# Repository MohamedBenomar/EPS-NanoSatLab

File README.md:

# Electrical Power System (EPS) for the NanoSatLab of the Universitat Politècnica de Catalunya (UPC)

Study and validate a design of a Electrical Power System for Nanosatellites using Supercapacitors technology as a source for systems that require high currents for a short time, together with Lithium-Ion batteries.

## Table of Contents

- [CADS](#cads)
- [Docs](#docs)
- [Firmware](#firmware)
- [Hardware](#hardware)
- [Validation](#validation)

## CADS

This folder section the 3D model of the designed PCB and the 3D model of an encapsulate for the system.

## Docs

This section includes the datasheets of the components used in the design, a real picture of the system indicating the differents blocks and the paper about the project.

## Firmware

This section includes the firmware for the ESP using an STM32 microcontroller.

## Hardware

This section includes the hardware files of the system using the open-source software KiCad.

## Validation

This section contains the validation report of the system.

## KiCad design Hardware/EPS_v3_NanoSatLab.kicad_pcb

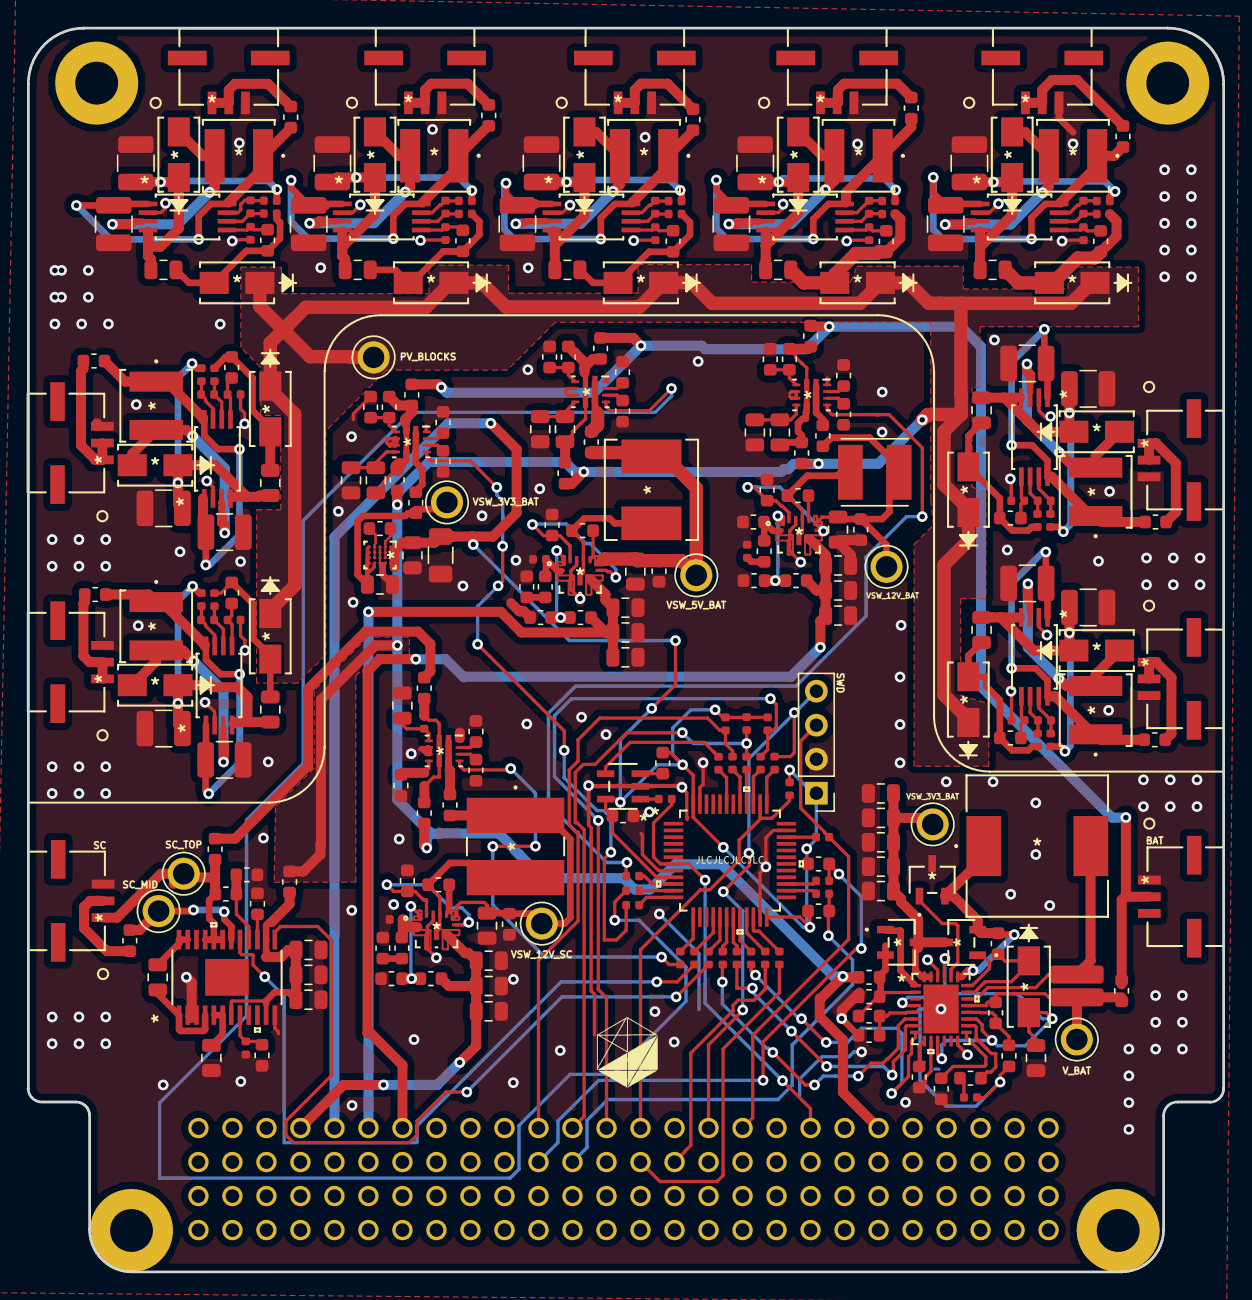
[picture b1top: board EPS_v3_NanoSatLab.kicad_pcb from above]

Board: 2 copper layers, 89.3 x 92.9 mm, 295 parts (0 on the bottom side), 198 nets.

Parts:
C201, C301, C302, C305, C306, C307, C308, C309, C313, C314, C317: 100 nF; C_0603_1608Metric
C303, C304, C312, C322, C324, C325, C327, C333, C401, C403, C404, C405, C502, C503, C505, C506, C508, C509: 10 uF; C_0805_2012Metric
C310, C311, C318: 2.2 uF; C_0603_1608Metric
C315, C316: 47 nF; C_0603_1608Metric
C319, C320: 62 pF; C_0402_1005Metric
C321, C323, C326, C330, C331, C332: 22 uF; C_0805_2012Metric
C328: 39 nF; C_0402_1005Metric
C329: 82 pF; C_0603_1608Metric
C334: 47 uF; C_1206_3216Metric
C402: 470 pF; C_0402_1005Metric
C501: 0.1 uF; C_0603_1608Metric
C504: 0.01 uF; C_0402_1005Metric
C507: 0.22 uF; C_0603_1608Metric
C601, C602, C603, C610, C611, C612, C619, C620, C621: 100 uF; C_1210_3225Metric
C604, C605, C606, C613, C614, C615, C622, C623, C624: 1 uF; C_0402_1005Metric
C607, C608, C609, C616, C617, C618, C625, C626, C627: 150 uF; C_1210_3225Metric
D501: 1A; DO-214BA-2
D601, D602, D603, D604, D605, D606, D607, D608, D609, D610, D611, D612, D613, D614, D615, D616, D617, D618: Vf=0.3V and If=3A; DO-214AB-2
J101, J102, J103, J104, J105, J106, J107, J108, J109, J111, J112: 502382-0370; MOLEX_502382-0370
J110: PC104
J201: SWD; PinHeader_1x04_P2.54mm_Vertical
L301: 3.2 uH; IND_FP3-3R3-R
L302: 6 uH; PM628S-100
L303: 2.7 uH; IND_LQH5BPN2R7NT0L
L304: 1 uH; L_0603_1608Metric
L401: 3.3 uH; L_0805_2012Metric
L501: 2.1 uH; NR10050T2R1N
L601, L602, L603, L604, L605, L606, L607, L608, L609: 47 uH; NRS5020T4R7MMGJ
Q501: INFET; DMN1019USN-7(TSOT-26-6)
Q502: T_NMOS; DMN1019USN-7(TSOT-26-6)
Q503: B_NMOS; DMN1019USN-7(TSOT-26-6)
R201, R202, R203, R204: 100 kΩ; R_0402_1005Metric
R205, R211, R227, R311, R312, R319, R320, R328, R329: 10 kΩ; R_0603_1608Metric
R206, R207, R208, R209, R210, R212, R213, R214, R215, R216, R217, R218, R219, R220, R221, R224, R225, R226: 0 Ω; R_0402_1005Metric
R222, R223: 33 Ω; R_0402_1005Metric
R301, R302, R303, R304, R315, R316, R321, R322, R323, R324, R330, R338, R401, R404, R407, R501, R510, R601, R602, R603, R619, R620, R621, R637, R638, R639: 0 Ω; R_0603_1608Metric
R305, R307: 12 kΩ; R_0402_1005Metric
R306: 40.2 kΩ; R_0603_1608Metric
R308: 7.5 kΩ; R_0805_2012Metric
R309, R317, R326: 5.1 kΩ; R_0805_2012Metric
R310, R318, R327: 15 kΩ; R_0805_2012Metric
R313, R314, R325, R331: 18 kΩ; R_0603_1608Metric
R332: 19.6 kΩ; R_0603_1608Metric
R333: 20.5 kΩ; R_0603_1608Metric
R334: 357 kΩ; R_0603_1608Metric
R335, R337, R341: 48.7 kΩ; R_0603_1608Metric
R336, R340: 931 kΩ; R_0603_1608Metric
R339: 34 kΩ; R_0603_1608Metric
R402: 3.57 kΩ; R_0603_1608Metric
R403: 142 kΩ; R_0603_1608Metric
R405: 2.21 MΩ; R_0603_1608Metric
R406: 301 kΩ; R_0603_1608Metric
R502: 1.5 MΩ; R_0603_1608Metric
R503, R507, R508: 1 MΩ; R_0603_1608Metric
R504: 86.6 kΩ; R_0603_1608Metric
R505: 75 kΩ; R_0603_1608Metric
R506: 3.36 kΩ; R_0603_1608Metric
R509: 22 mΩ; R_0815_2038Metric
R604, R605, R606, R607, R608, R609, R622, R623, R624, R625, R626, R627, R640, R641, R642, R643, R644, R645: 1 kΩ; R_0402_1005Metric
R610, R611, R612, R628, R629, R630, R646, R647, R648: 33.2 mΩ; R_0805_2012Metric
R613, R615, R617, R631, R633, R635, R649, R651, R653: 2 MΩ; R_0603_1608Metric
R614, R616, R618, R632, R634, R636, R650, R652, R654: 680 kΩ; R_0402_1005Metric
TP301, TP302, TP303, TP304, TP401, TP402, TP501, TP502, TP601: TestPoint; TESTPOINT_5013
U201: STM32L412C8T6
U202: MCP1320T-29LE_OT; MCP1320T-29LE&slash_OT
U301, U302, U303, U306: TPS2121RUXR
U304, U305, U307: TPS61288RQQR
U308: YFF0020AJAF; TPS630242YFFR
U401: LTC3128; LTC3128EFE-PBF
U501: LTC4013EUFD-PBF
U601, U602, U603, U604, U605, U606, U607, U608, U609: SPV1040T

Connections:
/5V_BAT: C321.1, C323.1, C326.1, J110.P$41, R334.1, U304.5
/12V_BAT: C330.1, C331.1, C332.1, J110.P$39, R340.1, U307.5
/12V_SC: C322.1, C324.1, C327.1, J110.P$45, R336.1, U305.5
/EPS - Batteries/BAT_CHG_ISMON: R217.2, U501.6
/EPS - Batteries/BAT_CHG_STAT0: R218.2, U501.7
/EPS - Batteries/BAT_CHG_STAT1: R210.2, U501.8
/EPS - Batteries/INTVCC: C509.2, D501.2, U501.4, U501.11, U501.17, U501.25
/EPS - Batteries/V_BAT: J111.2, R304.2, R316.2, R324.2, R510.1
/EPS - Converters/SW_3V3_BAT_uC: R213.2, U306.9
/EPS - Converters/SW_5V_BAT_uC: R207.2, U302.9
/EPS - Converters/SW_12V_BAT_uC: R212.2, U303.9
/EPS - Converters/SW_12V_SC_uC: R208.2, U301.9
/EPS - Converters/VSW_3V3_BAT: C325.1, R338.1, R338.2, TP304.1, U306.1, U306.8, U308.D4, U308.E1, U308.E2, U308.E3, U308.E4
/EPS - Converters/VSW_5V_BAT: R322.2, U302.1, U302.8
/EPS - Converters/VSW_12V_BAT: R330.2, U303.1, U303.8
/EPS - Converters/VSW_12V_SC: R321.2, U301.1, U301.8
/EPS - MCU/*PFO_SC: R209.2, U401.13
/EPS - MCU/PGOOD_SC: R214.2, U401.17
/EPS - MCU/WDI: R221.2, U202.4
/EPS – MPPT/PV_Array_X_1: J101.1, J101.2, R601.2
/EPS – MPPT/PV_Array_X_2: J104.1, J104.2, R619.2
/EPS – MPPT/PV_Array_X_3: J107.1, J107.2, R637.2
/EPS – MPPT/PV_Array_Y_1: J102.1, J102.2, R602.2
/EPS – MPPT/PV_Array_Y_2: J105.1, J105.2, R620.2
/EPS – MPPT/PV_Array_Y_3: J108.1, J108.2, R638.2
/EPS – MPPT/PV_Array_Z_1: J103.1, J103.2, R603.2
/EPS – MPPT/PV_Array_Z_2: J106.1, J106.2, R621.2
/EPS – MPPT/PV_Array_Z_3: J109.1, J109.2, R639.2
/I2C2_SCL: J110.P$30, R211.1, R224.2
/I2C2_SDA: J110.P$32, R205.1, R225.2
/LPUART1_RX: J110.P$24, R222.2
/LPUART1_TX: J110.P$26, R223.2
/NRST_MCU: J110.P$15, R226.2, U201.7
/PV_BLOCKS: D604.1, D605.1, D606.1, D610.1, D611.1, D612.1, D616.1, D617.1, D618.1, J110.P$11, R301.2, R303.2, R315.2, R323.2, R401.2, R501.2, TP601.1
/SC_MID: J112.2, R404.1, R404.2, TP401.1, U401.18
/SC_TOP: J112.1, R302.2, R405.1, R407.1, R407.2, TP402.1, U401.19, U401.20, U401.21
/SPI1_MISO: J110.P$29, R203.1, R206.2
/SPI1_MOSI: J110.P$31, R201.1, R220.2
/SPI1_NSS: J110.P$25, R202.1, U201.38
/SPI1_SCK: J110.P$27, R204.1, R219.2
/SWCLK: J110.P$21, J201.4, R216.2
/SWDIO: J110.P$19, J201.3, R215.2
GND: C201.2, C301.1, C302.1, C303.2, C304.2, C305.2, C306.2, C307.1, C310.2, C311.2, C312.2, C313.2, C314.1, C315.2, C316.2, C318.2, C319.2, C320.2, C321.2, C322.2, C323.2, C324.2, C325.2, C326.2, C327.2, C328.2, C329.2, C330.2, C331.2, C332.2, C333.2, C334.2, C401.2, C402.2, C403.2, C404.2, C405.2, C501.1, C502.2, C503.2, C505.2, C506.2, C508.2, C509.1, C601.2, C602.2, C603.2, C607.2, C608.2, C609.2, C610.2, C611.2, C612.2, C616.2, C617.2, C618.2, C619.2, C620.2, C621.2, C625.2, C626.2, C627.2, J101.3, J102.3, J103.3, J104.3, J105.3, J106.3, J107.3, J108.3, J109.3, J111.1, J112.3, J201.2, Q503.3, R306.1, R308.1, R310.1, R312.1, R313.2, R314.2, R318.1, R320.1, R325.2, R327.1, R329.1, R331.2, R335.2, R337.2, R341.2, R402.2, R403.2, R406.2, R503.2, R504.2, R505.2, R614.2, R616.2, R618.2, R632.2, R634.2, R636.2, R650.2, R652.2, R654.2, U201.8, U201.23, U201.35, U201.47, U202.2, U301.4, U301.5, U301.12, U302.4, U302.5, U302.12, U303.4, U303.5, U303.12, U304.3, U304.10, U305.3, U305.10, U306.4, U306.5, U306.12, U307.3, U307.10, U308.B4, U308.C1, U308.C2, U308.C3, U308.C4, U401.2, U401.3, U401.12, U501.10, U501.14, U501.26, U601.2, U602.2, U603.2, U604.2, U605.2, U606.2, U607.2, U608.2, U609.2
unnamed: C301.2, U301.11
unnamed: C302.2, U302.11
unnamed: C303.1, C305.1, L301.1, R322.1, TP301.1, U304.7
unnamed: C304.1, C306.1, L302.1, R321.1, TP302.1, U305.7
unnamed: C307.2, U303.11
unnamed: C308.1, L301.2, U304.4, U304.9
unnamed: C308.2, U304.8
unnamed: C309.1, L302.2, U305.4, U305.9
unnamed: C309.2, U305.8
unnamed: C310.1, U304.6, U304.11
unnamed: C311.1, U305.6, U305.11
unnamed: C312.1, C313.1, L303.1, R330.1, TP303.1, U307.7
unnamed: C314.2, U306.11
unnamed: C315.1, R332.2
unnamed: C316.1, R333.2
unnamed: C317.1, L303.2, U307.4, U307.9
unnamed: C317.2, U307.8
unnamed: C318.1, U307.6, U307.11
unnamed: C319.1, R332.1, U304.2
unnamed: C320.1, R333.1, U305.2
unnamed: C328.1, R339.2
unnamed: C329.1, R339.1, U307.2
unnamed: C401.1, C403.1, C404.1, R401.1, U401.7, U401.11, U401.14
unnamed: C402.1, R402.1, U401.8
unnamed: C405.1, U401.5, U401.6
unnamed: C501.2, Q501.2, R501.1, R502.1, U501.2
unnamed: C502.1, C503.1, C505.1, C506.1, C508.1, Q501.3, Q502.3, TP501.1, U501.27, U501.28
unnamed: C504.1, R508.2, U501.29
unnamed: C504.2, R506.1
unnamed: C507.1, L501.1, Q502.2, Q503.2, U501.23
unnamed: C507.2, D501.1, U501.21
unnamed: C601.1, L601.1, R601.1, U601.1, U601.8
unnamed: C602.1, L602.1, R602.1, U602.1, U602.8
unnamed: C603.1, L603.1, R603.1, U603.1, U603.8
unnamed: C604.1, R604.2, U601.7
unnamed: C604.2, R605.2, U601.6
unnamed: C605.1, R606.2, U602.7
unnamed: C605.2, R607.2, U602.6
unnamed: C606.1, R608.2, U603.7
unnamed: C606.2, R609.2, U603.6
unnamed: C607.1, D601.1, R604.1, R610.2, U601.4
unnamed: C608.1, D602.1, R606.1, R611.2, U602.4
unnamed: C609.1, D603.1, R608.1, R612.2, U603.4
unnamed: C610.1, L604.1, R619.1, U604.1, U604.8
unnamed: C611.1, L605.1, R620.1, U605.1, U605.8
unnamed: C612.1, L606.1, R621.1, U606.1, U606.8
unnamed: C613.1, R622.2, U604.7
unnamed: C613.2, R623.2, U604.6
unnamed: C614.1, R624.2, U605.7
unnamed: C614.2, R625.2, U605.6
unnamed: C615.1, R626.2, U606.7
unnamed: C615.2, R627.2, U606.6
unnamed: C616.1, D607.1, R622.1, R628.2, U604.4
unnamed: C617.1, D608.1, R624.1, R629.2, U605.4
unnamed: C618.1, D609.1, R626.1, R630.2, U606.4
unnamed: C619.1, L607.1, R637.1, U607.1, U607.8
unnamed: C620.1, L608.1, R638.1, U608.1, U608.8
unnamed: C621.1, L609.1, R639.1, U609.1, U609.8
unnamed: C622.1, R640.2, U607.7
unnamed: C622.2, R641.2, U607.6
unnamed: C623.1, R642.2, U608.7
unnamed: C623.2, R643.2, U608.6
unnamed: C624.1, R644.2, U609.7
unnamed: C624.2, R645.2, U609.6
unnamed: C625.1, D613.1, R640.1, R646.2, U607.4
unnamed: C626.1, D614.1, R642.1, R647.2, U608.4
unnamed: C627.1, D615.1, R644.1, R648.2, U609.4
unnamed: D601.2, L601.2, U601.3
unnamed: D602.2, L602.2, U602.3
unnamed: D603.2, L603.2, U603.3
unnamed: D604.2, R605.1, R610.1, R613.1
unnamed: D605.2, R607.1, R611.1, R615.1
unnamed: D606.2, R609.1, R612.1, R617.1
unnamed: D607.2, L604.2, U604.3
unnamed: D608.2, L605.2, U605.3
unnamed: D609.2, L606.2, U606.3
unnamed: D610.2, R623.1, R628.1, R631.1
unnamed: D611.2, R625.1, R629.1, R633.1
unnamed: D612.2, R627.1, R630.1, R635.1
unnamed: D613.2, L607.2, U607.3
unnamed: D614.2, L608.2, U608.3
unnamed: D615.2, L609.2, U609.3
unnamed: D616.2, R641.1, R646.1, R649.1
unnamed: D617.2, R643.1, R647.1, R651.1
unnamed: D618.2, R645.1, R648.1, R653.1
unnamed: L304.1, U308.D1, U308.D2, U308.D3
unnamed: L304.2, U308.B1, U308.B2, U308.B3
unnamed: L401.1, U401.1, U401.4
unnamed: L401.2, U401.23, U401.24
unnamed: L501.2, R509.1, U501.20
unnamed: Q501.1, U501.1
unnamed: Q502.1, U501.22
unnamed: Q503.1, U501.24
unnamed: R206.1, U201.40
unnamed: R207.1, U201.11
unnamed: R208.1, U201.13
unnamed: R209.1, U201.17
unnamed: R210.1, U201.20
unnamed: R212.1, U201.10
unnamed: R213.1, U201.12
unnamed: R214.1, U201.16
unnamed: R215.1, U201.34
unnamed: R216.1, U201.37
unnamed: R217.1, U201.18
unnamed: R218.1, U201.19
unnamed: R219.1, U201.39
unnamed: R220.1, U201.41
unnamed: R221.1, U201.43
unnamed: R222.1, U201.21
unnamed: R223.1, U201.22
unnamed: R224.1, U201.26
unnamed: R225.1, U201.27
unnamed: R226.1, U202.1
unnamed: R227.1, U202.3
unnamed: R301.1, R305.1, U301.7
unnamed: R302.1, R307.1, U301.2
unnamed: R303.1, R309.1, U302.7
unnamed: R304.1, R311.1, U302.2
unnamed: R305.2, R306.2, U301.6
unnamed: R307.2, R308.2, U301.3
unnamed: R309.2, R310.2, U302.6
unnamed: R311.2, R312.2, U302.3
unnamed: R313.1, U301.10
unnamed: R314.1, U302.10
unnamed: R315.1, R317.1, U303.7
unnamed: R316.1, R319.1, U303.2
unnamed: R317.2, R318.2, U303.6
unnamed: R319.2, R320.2, U303.3
unnamed: R323.1, R326.1, U306.7
unnamed: R324.1, R328.1, U306.2
unnamed: R325.1, U303.10
unnamed: R326.2, R327.2, U306.6
unnamed: R328.2, R329.2, U306.3
unnamed: R331.1, U306.10
unnamed: R334.2, R335.1, U304.1
unnamed: R336.2, R337.1, U305.1
unnamed: R340.2, R341.1, U307.1
unnamed: R403.1, U401.15
unnamed: R405.2, R406.1, U401.16
unnamed: R502.2, R503.1, U501.5
unnamed: R504.1, U501.15
unnamed: R505.1, U501.9
unnamed: R506.2, U501.16
unnamed: R507.1, R509.2, R510.2, TP502.1, U501.19
unnamed: R507.2, R508.1, U501.18
unnamed: R613.2, R614.1, U601.5
unnamed: R615.2, R616.1, U602.5
unnamed: R617.2, R618.1, U603.5
unnamed: R631.2, R632.1, U604.5
unnamed: R633.2, R634.1, U605.5
unnamed: R635.2, R636.1, U606.5
unnamed: R649.2, R650.1, U607.5
unnamed: R651.2, R652.1, U608.5
unnamed: R653.2, R654.1, U609.5
VDD: C201.1, C333.1, C334.1, J110.P$43, J201.1, R201.2, R202.2, R203.2, R204.2, R205.2, R211.2, R227.2, U201.9, U201.24, U201.48, U202.5, U308.A1, U308.A2, U308.A3, U308.A4

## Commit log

2024-02-26 README.md

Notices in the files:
parts and their libraries:
Copyright 2016 Accelerated Designs. All rights reserved.
